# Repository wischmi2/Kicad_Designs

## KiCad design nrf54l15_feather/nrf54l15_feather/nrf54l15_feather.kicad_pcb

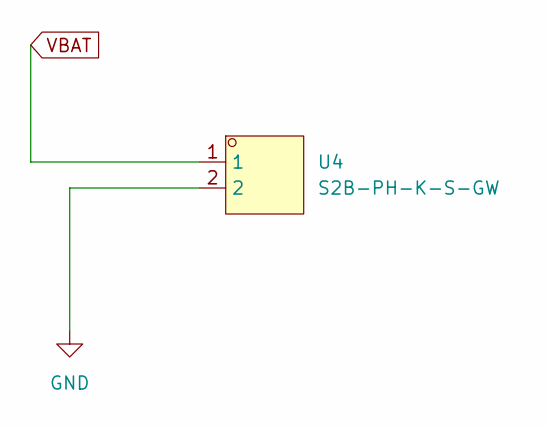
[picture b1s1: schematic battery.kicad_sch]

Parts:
U4: S2B-PH-K-S-GW; CONN-TH_S2B-PH-K-S-GW; MPN S2B-PH-K-S-GW; LCSC Part C157932

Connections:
GND: U4.2; also elsewhere on the board
VBAT: U4.1; also elsewhere on the board

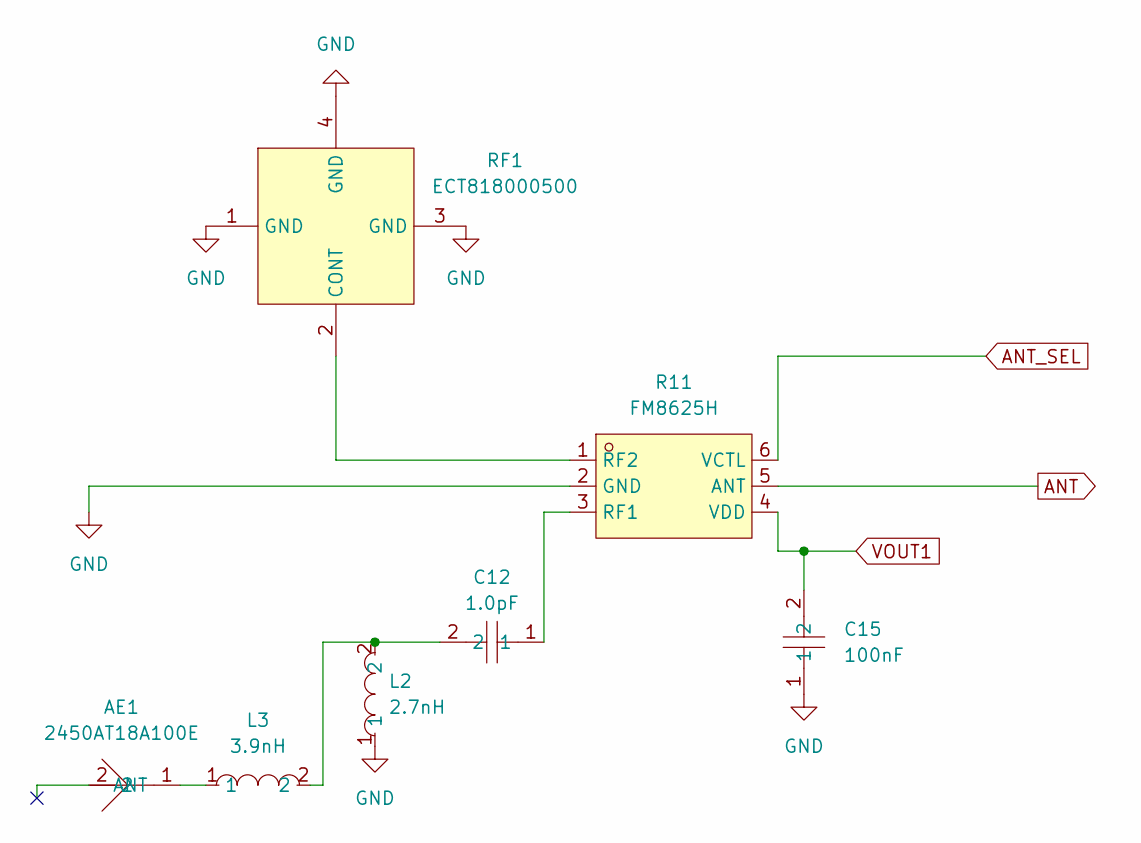
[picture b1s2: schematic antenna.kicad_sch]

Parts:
AE1: 2450AT18A100E; ANT-SMD_L3.2-W1.6; MPN 2450AT18A100E; LCSC Part C89334
C12: 1.0pF; C0201; MPN GJM0335C1E1R0WB01D; LCSC Part C185624
C15: 100nF; C0603; MPN CC0603KRX7R9BB104; LCSC Part C14663
L2: 2.7nH; L0201; MPN LQP03HQ2N7B02D; LCSC Part C7216765
L3: 3.9nH; L0201; MPN LQP03HQ3N9B02D; LCSC Part C337939
R11: FM8625H; DFN-6_L1.1-W0.7-P0.40-BL; MPN FM8625H; LCSC Part C2857391
RF1: ECT818000500; ANT-SMD_ECT818000500; MPN ECT818000500; LCSC Part C437254

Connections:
ANT: R11.5 (ANT); also elsewhere on the board
ANT_SEL: R11.6 (VCTL); also elsewhere on the board
GND: C15.1, L2.1, R11.2 (GND), RF1.1 (GND), RF1.3 (GND), RF1.4 (GND); also elsewhere on the board
unnamed: AE1.1 (ANT_1), L3.1
unnamed: C12.2, L2.2, L3.2
unnamed: C12.1, R11.3 (RF1)
unnamed: R11.1 (RF2), RF1.2 (CONT)
VOUT1: C15.2, R11.4 (VDD); also elsewhere on the board

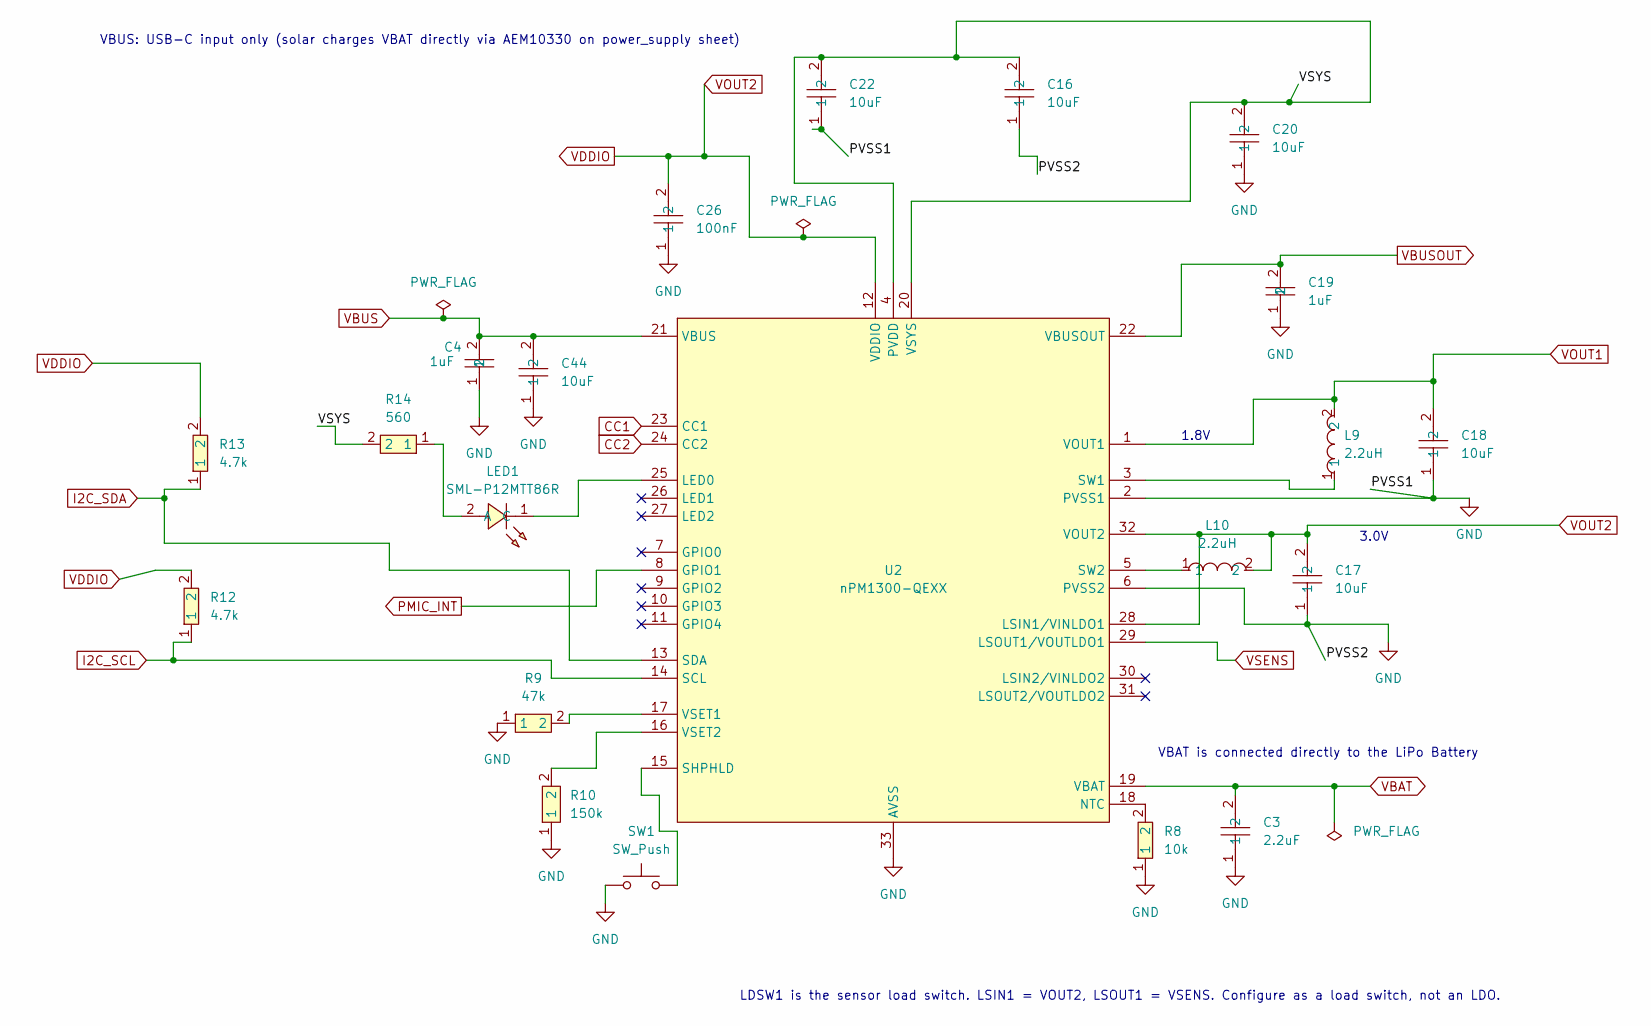
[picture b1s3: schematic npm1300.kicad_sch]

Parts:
C3: 2.2uF; C0603; MPN CL10A225KB8NNNC; LCSC Part C913904
C4, C19: 1uF; C0402; MPN CL05A105KO5NNNC; LCSC Part C29266
C16: 10uF; C0603; MPN CC0603MRX5R8BB106; LCSC Part C596327
C17, C18, C20, C22, C44: 10uF; C0805; MPN CL21A106KAYNNNE; LCSC Part C15850
C26: 100nF; C0603; MPN CC0603KRX7R9BB104; LCSC Part C14663
L9, L10: 2.2uH; L0603; MPN LSCNB1608HKT2R2MD; LCSC Part C6079477
LED1: SML-P12MTT86R; LED-SMD_L1.0-W0.6-RD_SML-P12YTT86RR; MPN SML-P12MTT86R; LCSC Part C510304
R8: 10k; R0402; MPN RT0402BRD0710KL; LCSC Part C190095
R9: 47k; R0603; MPN FRC0603F4702TS; LCSC Part C2907042
R10: 150k; R0603; MPN FRC0603F1503TS; LCSC Part C2906993
R12, R13: 4.7k; R0402; MPN RC0402FR-074K7L; LCSC Part C105871
R14: 560; R0402; MPN FRC0402F5600TS; LCSC Part C2909370
SW1: SW_Push; SW_SPST_B3U-1000P; MPN B3U-1000P
U2: nPM1300-QEXX; QFN-32-1EP_5x5mm_P0.5mm_EP3.6x3.6mm_ThermalVias; MPN nPM1300-QEAA-R7

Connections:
/npm1300/VSYS: C16.2, C20.2, C22.2, R14.2, U2.4 (PVDD), U2.20 (VSYS)
CC1: U2.23 (CC1); also elsewhere on the board
CC2: U2.24 (CC2); also elsewhere on the board
GND: C3.1, C4.1, C16.1, C17.1, C18.1, C19.1, C20.1, C22.1, C26.1, C44.1, R8.1, R9.1, R10.1, SW1.1, U2.2 (PVSS1), U2.6 (PVSS2), U2.33 (AVSS); also elsewhere on the board
I2C_SCL: R12.1, U2.14 (SCL); also elsewhere on the board
I2C_SDA: R13.1, U2.13 (SDA); also elsewhere on the board
unnamed: LED1.2 (A), R14.1
unnamed: LED1.1 (C), U2.25 (LED0)
unnamed: R8.2, U2.18 (NTC)
unnamed: SW1.2, U2.15 (SHPHLD)
unnamed: L9.1, U2.3 (SW1)
unnamed: L10.1, U2.5 (SW2)
unnamed: R9.2, U2.17 (VSET1)
unnamed: R10.2, U2.16 (VSET2)
PMIC_INT: U2.8 (GPIO1); also elsewhere on the board
VBAT: C3.2, U2.19 (VBAT); also elsewhere on the board
VBUS: C4.2, C44.2, U2.21 (VBUS); also elsewhere on the board
VBUSOUT: C19.2, U2.22 (VBUSOUT)
VDDIO: C17.2, C26.2, L10.2, R12.2, R13.2, U2.12 (VDDIO), U2.28 (LSIN1/VINLDO1), U2.32 (VOUT2); also elsewhere on the board
VOUT1: C18.2, L9.2, U2.1 (VOUT1); also elsewhere on the board
VSENS: U2.29 (LSOUT1/VOUTLDO1); also elsewhere on the board

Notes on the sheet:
1.8V
VBAT is connected directly to the LiPo Battery
LDSW1 is the sensor load switch. LSIN1 = VOUT2, LSOUT1 = VSENS. Configure as a load switch, not an LDO.
VBUS: USB-C input only (solar charges VBAT directly via AEM10330 on power_supply sheet)
3.0V

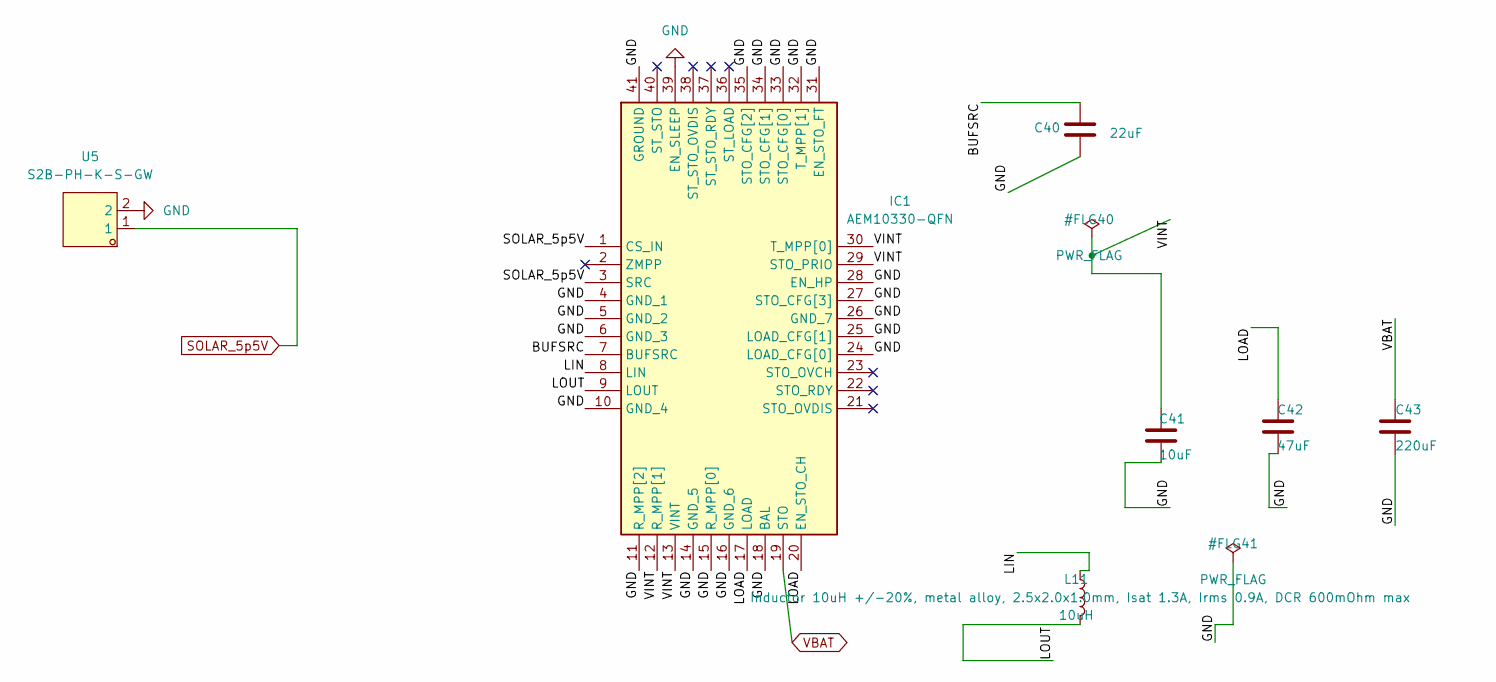
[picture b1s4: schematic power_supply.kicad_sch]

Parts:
C40: 22uF; C_0603_1608Metric; MPN GRM188R61A226ME15D
C41: 10uF; C_0402_1005Metric; MPN GRM155R60J106ME15
C42: 47uF; C_0603_1608Metric; MPN GRM188R60J476ME15D
C43: 220uF; C_1206_3216Metric; MPN MSASJ31LBB5227MTCA01
IC1: AEM10330-QFN; QFN40P500X500X85-41N-D; Mouser Part Number 120-AEM10330-QFN
L11: 10uH; L_Sunlord_SWPA252010S; MPN DFE252010F-100M=P2; LCSC Part C701155
U5: S2B-PH-K-S-GW; CONN-TH_S2B-PH-K-S-GW; MPN S2B-PH-K-S-GW; LCSC Part C157932

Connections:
/Solar/BUFSRC: C40.1, IC1.7 (BUFSRC)
/Solar/LIN: IC1.8 (LIN), L11.1
/Solar/LOAD: C42.1, IC1.17 (LOAD), IC1.20 (EN_STO_CH)
/Solar/LOUT: IC1.9 (LOUT), L11.2
/Solar/VINT: C41.1, IC1.12 (R_MPP[1]), IC1.13 (VINT), IC1.29 (STO_PRIO), IC1.30 (T_MPP[0])
GND: C40.2, C41.2, C42.2, C43.2, IC1.4 (GND_1), IC1.5 (GND_2), IC1.6 (GND_3), IC1.10 (GND_4), IC1.11 (R_MPP[2]), IC1.14 (GND_5), IC1.15 (R_MPP[0]), IC1.16 (GND_6), IC1.18 (BAL), IC1.24 (LOAD_CFG[0]), IC1.25 (LOAD_CFG[1]), IC1.26 (GND_7), IC1.27 (STO_CFG[3]), IC1.28 (EN_HP), IC1.31 (EN_STO_FT), IC1.32 (T_MPP[1]), IC1.33 (STO_CFG[0]), IC1.34 (STO_CFG[1]), IC1.35 (STO_CFG[2]), IC1.39 (EN_SLEEP), IC1.41 (GROUND), U5.2; also elsewhere on the board
SOLAR_5p5V: IC1.1 (CS_IN), IC1.3 (SRC), U5.1
VBAT: C43.1, IC1.19 (STO); also elsewhere on the board

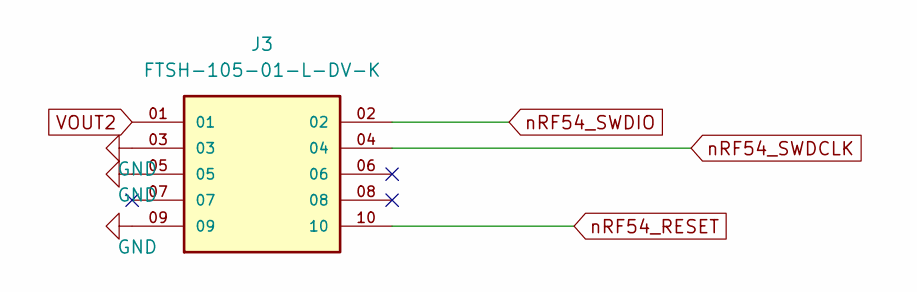
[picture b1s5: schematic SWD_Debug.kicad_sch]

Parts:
J3: FTSH-105-01-L-DV-K; SAMTEC_FTSH-105-01-L-DV-K; MPN FTSH-105-01-L-DV-K-TR

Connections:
GND: J3.03, J3.05, J3.09; also elsewhere on the board
VDDIO: J3.01; also elsewhere on the board
nRF54_RESET: J3.10; also elsewhere on the board
nRF54_SWDCLK: J3.04; also elsewhere on the board
nRF54_SWDIO: J3.02; also elsewhere on the board

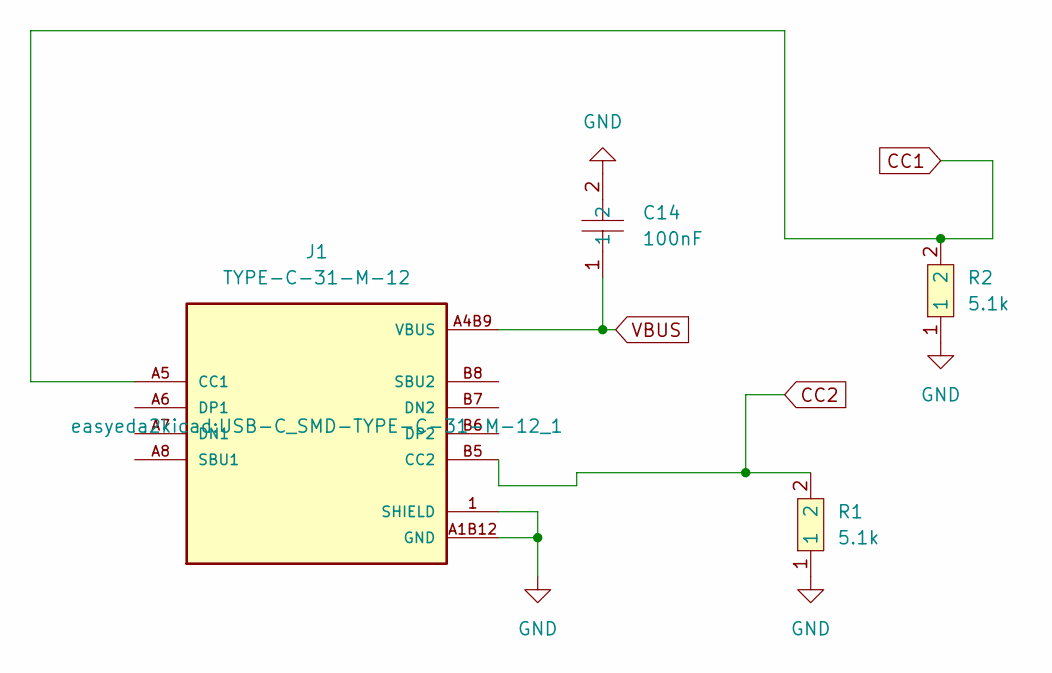
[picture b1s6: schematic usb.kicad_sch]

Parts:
C14: 100nF; C0603; MPN CC0603KRX7R9BB104; LCSC Part C14663
J1: TYPE-C-31-M-12; USB-C_SMD-TYPE-C-31-M-12_1; PARTREV 2020.12.08
R1, R2: 5.1k; R0402; MPN RCA025K1FLF; LCSC Part C22369457

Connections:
CC1: J1.A5 (CC1), R2.2; also elsewhere on the board
CC2: J1.B5 (CC2), R1.2; also elsewhere on the board
GND: C14.2, J1.1 (SHIELD), J1.2 (SHIELD), J1.3 (SHIELD), J1.4 (SHIELD), J1.A1B12 (GND), J1.B1A12 (GND), R1.1, R2.1; also elsewhere on the board
VBUS: C14.1, J1.A4B9 (VBUS), J1.B4A9 (VBUS); also elsewhere on the board

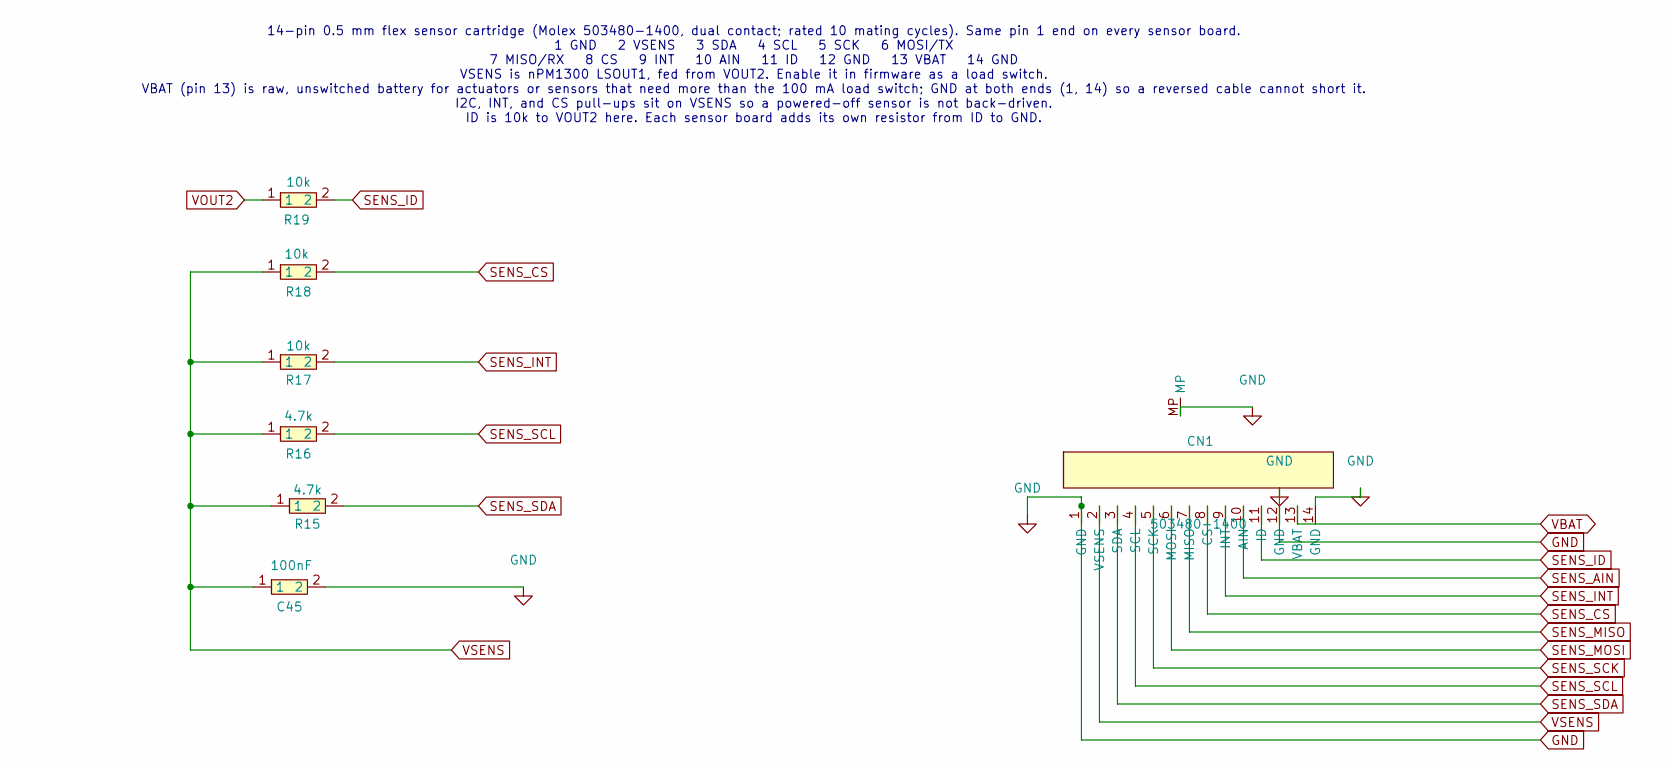
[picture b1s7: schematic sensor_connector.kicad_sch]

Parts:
C45: 100nF; C0402; MPN CL05B104KO5NNNC
CN1: 503480-1400; Molex_503480-1400_1x14-1MP_P0.50mm_Horizontal; MPN 503480-1400
R15, R16: 4.7k; R0402; MPN RC0402FR-074K7L
R17, R18, R19: 10k; R0402; MPN RT0402BRD0710KL; LCSC Part C190095

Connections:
GND: C45.2, CN1.1 (GND), CN1.12 (GND), CN1.14 (GND), CN1.MP; also elsewhere on the board
SENS_AIN: CN1.10 (AIN); also elsewhere on the board
SENS_CS: CN1.8 (CS), R18.2; also elsewhere on the board
SENS_ID: CN1.11 (ID), R19.2; also elsewhere on the board
SENS_INT: CN1.9 (INT), R17.2; also elsewhere on the board
SENS_MISO: CN1.7 (MISO); also elsewhere on the board
SENS_MOSI: CN1.6 (MOSI); also elsewhere on the board
SENS_SCK: CN1.5 (SCK); also elsewhere on the board
SENS_SCL: CN1.4 (SCL), R16.2; also elsewhere on the board
SENS_SDA: CN1.3 (SDA), R15.2; also elsewhere on the board
VBAT: CN1.13 (VBAT); also elsewhere on the board
VDDIO: R19.1; also elsewhere on the board
VSENS: C45.1, CN1.2 (VSENS), R15.1, R16.1, R17.1, R18.1; also elsewhere on the board

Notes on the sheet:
14-pin 0.5 mm flex sensor cartridge (Molex 503480-1400, dual contact; rated 10 mating cycles). Same pin 1 end on every sensor board. 1 GND 2 VSENS 3 SDA 4 SCL 5 SCK 6 MOSI/TX 7 MISO/RX 8 CS 9 INT 10 AIN 11 ID 12 GND 13 VBAT 14 GND VSENS is nPM1300 LSOUT1, fed from VOUT2. Enable it in firmware as a 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

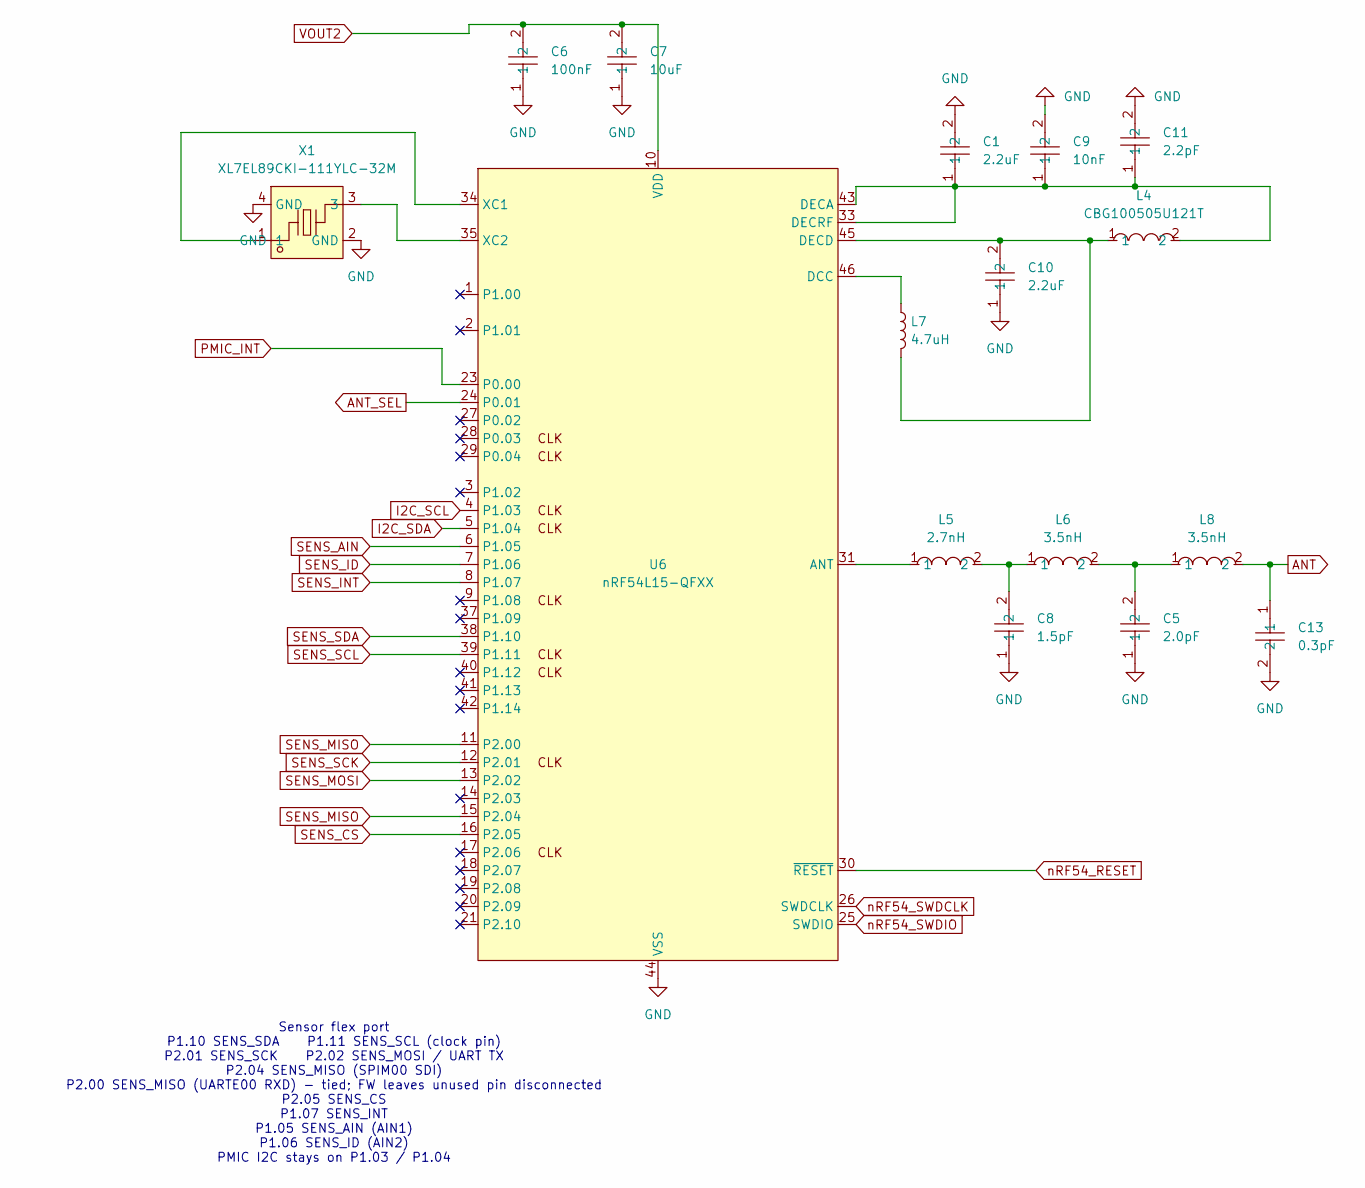
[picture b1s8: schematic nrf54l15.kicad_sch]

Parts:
C1, C10: 2.2uF; C0201; MPN GRM033R61A225KE47D; LCSC Part C335106
C5: 2.0pF; C0201; MPN GJM0335C1E2R0WB01D; LCSC Part C668326
C6: 100nF; C0603; MPN CC0603KRX7R9BB104; LCSC Part C14663
C7: 10uF; C0805; MPN CL21A106KAYNNNE; LCSC Part C15850
C8: 1.5pF; C0201; MPN GJM0335C1E1R5WB01D; LCSC Part C435397
C9: 10nF; C0402; MPN GCM155R71H103KA55D; LCSC Part C91601
C11: 2.2pF; C0201; MPN GJM0335C1E2R2WB01D; LCSC Part C710732
C13: 0.3pF; C0201; MPN GJM0335C1ER30WB01D; LCSC Part C161289
L4: CBG100505U121T; L0402; MPN CBG100505U121T; LCSC Part C92616
L5: 2.7nH; L0201; MPN LQP03HQ2N7B02D; LCSC Part C7216765
L6, L8: 3.5nH; L0201; MPN LQP03HQ3N5B02D; LCSC Part C3911055
L7: 4.7uH; L0603; MPN LQM18PH4R7MFRL; LCSC Number C1858257
U6: nRF54L15-QFXX; QFN-48-1EP_6x6mm_P0.4mm_EP4.6x4.6mm_ThermalVias; MPN nRF54L15-QFAA-R
X1: XL7EL89CKI-111YLC-32M; CRYSTAL-SMD_4P-L2.0-W1.6-BL; MPN XL7EL89CKI-111YLC-32M; LCSC Part C2965582

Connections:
ANT: C13.1, L8.2; also elsewhere on the board
ANT_SEL: U6.24 (P0.01); also elsewhere on the board
GND: C1.2, C5.1, C6.1, C7.1, C8.1, C9.2, C10.1, C11.2, C13.2, U6.32 (VSS_PA), U6.44 (VSS), U6.49 (VSS), X1.2 (GND), X1.4 (GND); also elsewhere on the board
I2C_SCL: U6.4 (P1.03); also elsewhere on the board
I2C_SDA: U6.5 (P1.04); also elsewhere on the board
unnamed: C5.2, L6.2, L8.1
unnamed: C8.2, L5.2, L6.1
unnamed: L5.1, U6.31 (ANT)
unnamed: L7.1, U6.46 (DCC)
unnamed: C1.1, C9.1, C11.1, L4.2, U6.33 (DECRF), U6.43 (DECA)
unnamed: C10.2, L4.1, L7.2, U6.45 (DECD)
unnamed: U6.34 (XC1), X1.1
unnamed: U6.35 (XC2), X1.3
PMIC_INT: U6.23 (P0.00); also elsewhere on the board
SENS_AIN: U6.6 (P1.05); also elsewhere on the board
SENS_CS: U6.16 (P2.05); also elsewhere on the board
SENS_ID: U6.7 (P1.06); also elsewhere on the board
SENS_INT: U6.8 (P1.07); also elsewhere on the board
SENS_MISO: U6.11 (P2.00), U6.15 (P2.04); also elsewhere on the board
SENS_MOSI: U6.13 (P2.02); also elsewhere on the board
SENS_SCK: U6.12 (P2.01); also elsewhere on the board
SENS_SCL: U6.39 (P1.11); also elsewhere on the board
SENS_SDA: U6.38 (P1.10); also elsewhere on the board
VDDIO: C6.2, C7.2, U6.10 (VDD), U6.22 (VDD), U6.36 (VDD), U6.47 (VDD), U6.48 (VDD); also elsewhere on the board
nRF54_RESET: U6.30 (~RESET); also elsewhere on the board
nRF54_SWDCLK: U6.26 (SWDCLK); also elsewhere on the board
nRF54_SWDIO: U6.25 (SWDIO); also elsewhere on the board

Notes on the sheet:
Sensor flex port P1.10 SENS_SDA P1.11 SENS_SCL (clock pin) P2.01 SENS_SCK P2.02 SENS_MOSI / UART TX P2.04 SENS_MISO (SPIM00 SDI) P2.00 SENS_MISO (UARTE00 RXD) - tied; FW leaves unused pin disconnected P2.05 SENS_CS P1.07 SENS_INT P1.05 SENS_AIN (AIN1) P1.06 SENS_ID (AIN2) PMIC I2C stays on P1.03 / 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

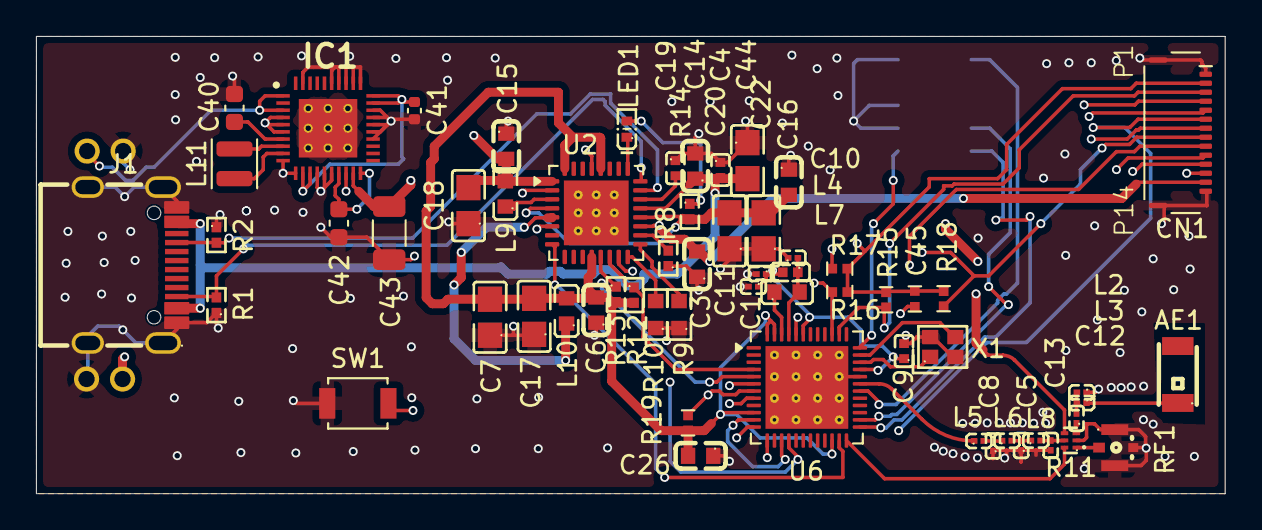
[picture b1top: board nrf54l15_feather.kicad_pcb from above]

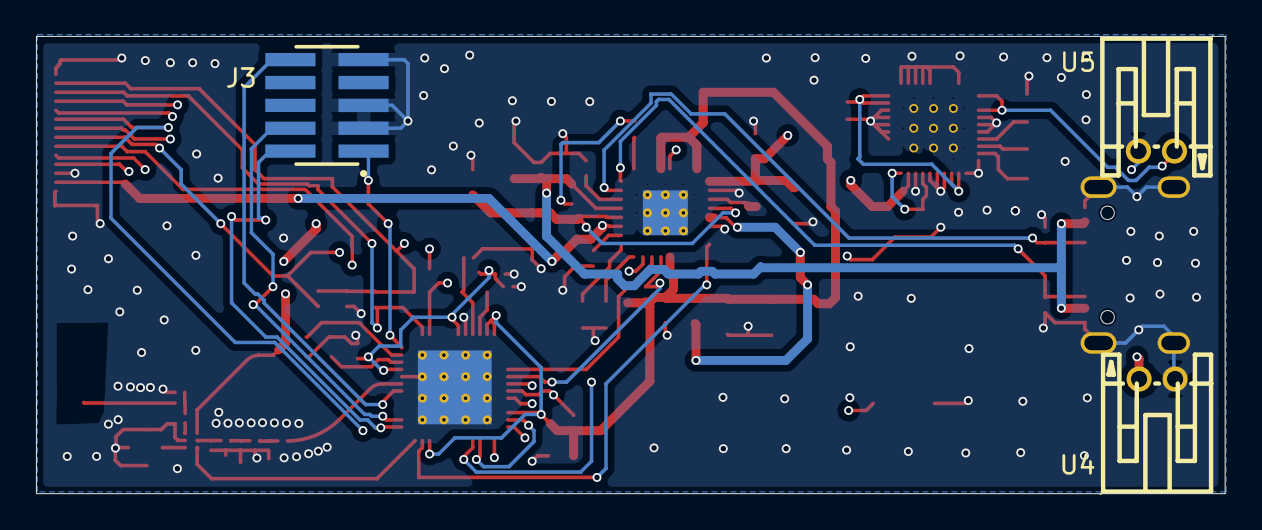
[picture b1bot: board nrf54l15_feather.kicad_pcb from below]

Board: 4 copper layers, 66.0 x 25.4 mm, 64 parts (3 on the bottom side), 53 nets.

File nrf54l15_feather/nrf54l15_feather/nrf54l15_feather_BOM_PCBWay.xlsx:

|  |  | nrf54l15_feather — PCB Assembly BOM
Item # | *Designator | *Qty | Manufacturer | *Mfg Part # | Description / Value | *Package/Footprint | Type | Your Instructions / Notes
1 | C45 | 1 | Samsung Electro-Mechanics | CL05B104KO5NNNC | CAP CER 100nF 16V X7R ±10% 0402 | 0402 | SMD | LCSC: C1525
2 | C6,C14,C15,C26 | 4 | YAGEO | CC0603KRX7R9BB104 | CAP CER 100nF 50V X7R ±10% 0603 | 0603 | SMD | LCSC: C14663
3 | C9 | 1 | Murata | GCM155R71H103KA55D | CAP CER 10nF 50V X7R ±10% 0402 | 0402 | SMD | LCSC: C91601
4 | C4,C19 | 2 | Samsung Electro-Mechanics | CL05A105KO5NNNC | CAP CER 1uF 16V X5R ±10% 0402 | 0402 | SMD | LCSC: C29266
5 | C1,C10 | 2 | Murata | GRM033R61A225KE47D | CAP CER 2.2uF 10V X5R ±10% 0201 | 0201 | SMD | LCSC: C335106
6 | C3 | 1 | Samsung Electro-Mechanics | CL10A225KB8NNNC | CAP CER 2.2uF 50V X5R ±10% 0603 | 0603 | SMD | LCSC: C913904
7 | C41 | 1 | Murata | GRM155R60J106ME15 | CAP CER 10uF 6.3V X5R ±20% 0402 | 0402 | SMD | No LCSC stock for ME15; GRM155R60J106ME44D (LCSC: C76991) acceptable alternate
8 | C16 | 1 | YAGEO | CC0603MRX5R8BB106 | CAP CER 10uF 25V X5R ±20% 0603 | 0603 | SMD | LCSC: C596327
9 | C7,C17,C18,C20,C22,C44 | 6 | Samsung Electro-Mechanics | CL21A106KAYNNNE | CAP CER 10uF 25V X5R ±10% 0805 | 0805 | SMD | LCSC: C15850
10 | C40 | 1 | Murata | GRM188R61A226ME15D | CAP CER 22uF 10V X5R ±20% 0603 | 0603 | SMD | LCSC: C84419
11 | C42 | 1 | Murata | GRM188R60J476ME15D | CAP CER 47uF 6.3V X5R ±20% 0603 | 0603 | SMD | LCSC: C140782
12 | C43 | 1 | Taiyo Yuden | MSASJ31LBB5227MTCA01 | CAP CER 220uF 1206 | 1206 | SMD | No LCSC part #; please quote sourcing
13 | C13 | 1 | Murata | GJM0335C1ER30WB01D | CAP CER 0.3pF 25V C0G ±0.05pF 0201 (RF) | 0201 | SMD | LCSC: C161289; RF match — do not substitute
14 | C12 | 1 | Murata | GJM0335C1E1R0WB01D | CAP CER 1.0pF 25V C0G ±0.05pF 0201 (RF) | 0201 | SMD | LCSC: C185624; RF match — do not substitute
15 | C8 | 1 | Murata | GJM0335C1E1R5WB01D | CAP CER 1.5pF 25V C0G ±0.05pF 0201 (RF) | 0201 | SMD | LCSC: C435397; RF match — do not substitute
16 | C5 | 1 | Murata | GJM0335C1E2R0WB01D | CAP CER 2.0pF 25V C0G ±0.05pF 0201 (RF) | 0201 | SMD | LCSC: C668326; RF match — do not substitute
17 | C11 | 1 | Murata | GJM0335C1E2R2WB01D | CAP CER 2.2pF 25V C0G ±0.05pF 0201 (RF) | 0201 | SMD | LCSC: C710732; RF match — do not substitute
18 | R14 | 1 | FOJAN | FRC0402F5600TS | RES 560 OHM 1% 0402 | 0402 | SMD | LCSC: C2909370
19 | R12,R13,R15,R16 | 4 | YAGEO | RC0402FR-074K7L | RES 4.7K OHM 1% 1/16W 0402 | 0402 | SMD | LCSC: C105871
20 | R1,R2 | 2 | HKR | RCA025K1FLF | RES 5.1K OHM 1% 0402 | 0402 | SMD | LCSC: C22369457
21 | R8,R17,R18,R19 | 4 | YAGEO | RT0402BRD0710KL | RES 10K OHM 0.1% 0402 | 0402 | SMD | LCSC: C190095
22 | R9 | 1 | FOJAN | FRC0603F4702TS | RES 47K OHM 1% 0603 | 0603 | SMD | LCSC: C2907042
23 | R10 | 1 | FOJAN | FRC0603F1503TS | RES 150K OHM 1% 0603 | 0603 | SMD | LCSC: C2906993
24 | L2,L5 | 2 | Murata | LQP03HQ2N7B02D | INDUCTOR RF 2.7nH ±0.1nH 0201 | 0201 | SMD | LCSC: C7216765; RF match — do not substitute
25 | L6,L8 | 2 | Murata | LQP03HQ3N5B02D | INDUCTOR RF 3.5nH ±0.1nH 0201 | 0201 | SMD | LCSC: C3911055; RF match — do not substitute
26 | L3 | 1 | Murata | LQP03HQ3N9B02D | INDUCTOR RF 3.9nH ±0.1nH 0201 | 0201 | SMD | LCSC: C337939; RF match — do not substitute
27 | L4 | 1 | FH (Fenghua) | CBG100505U121T | FERRITE BEAD 120 OHM @100MHz 0402 | 0402 | SMD | LCSC: C92616
28 | L9,L10 | 2 | Taiyo Yuden | LSCNB1608HKT2R2MD | INDUCTOR PWR 2.2uH ±20% 0603 | 0603 | SMD | LCSC: C6079477
29 | L7 | 1 | Murata | LQM18PH4R7MFRL | INDUCTOR PWR 4.7uH ±20% 0603 | 0603 | SMD | LCSC: C1858257
30 | L11 | 1 | Murata | DFE252010F-100M=P2 | INDUCTOR PWR 10uH ±20% 2.5x2.0mm | SMD 2.5x2.0mm | SMD | LCSC: C701155
31 | LED1 | 1 | ROHM | SML-P12MTT86R | LED RED 1006 (0402) | 1006 (0402) | SMD | LCSC: C510304; polarity per silkscreen
32 | U6 | 1 | Nordic Semiconductor | nRF54L15-QFAA-R | IC SoC BLE 2.4GHz ARM Cortex-M33 QFN-48 6x6mm | QFN-48 6x6mm P0.4mm | SMD | LCSC: C42458750; pin 1 per silkscreen
33 | U2 | 1 | Nordic Semiconductor | nPM1300-QEAA-R7 | IC PMIC CHARGER + 2x BUCK + 2x LDO/LOAD SW QFN-32 5x5mm | QFN-32 5x5mm P0.5mm | SMD | QFN-32 package required (do NOT substitute CSP variant); please quote sourcing.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
34 | IC1 | 1 | e-peas | AEM10330-QFN | IC ENERGY HARVESTING PMIC (solar) QFN-40 5x5mm | QFN-40 5x5mm P0.4mm | SMD | No LCSC part #; Mouser: 120-AEM10330-QFN; please quote sourcing. Pin 1 per silk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
35 | R11 | 1 | FM (Fuman) | FM8625H | IC RF SWITCH SPDT DFN-6 1.1x0.7mm | DFN-6 1.1x0.7mm P0.4mm | SMD | LCSC: C2857391; this is an IC (not a resistor) despite R designator. Pin 1 per 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
36 | X1 | 1 | YXC | XL7EL89CKI-111YLC-32M | CRYSTAL 32MHz SMD 2.0x1.6mm 4-pad | SMD 2.0x1.6mm | SMD | LCSC: C2965582
37 | AE1 | 1 | Johanson Technology | 2450AT18A100E | ANTENNA CHIP 2.45GHz 3.2x1.6mm | SMD 3.2x1.6mm | SMD | LCSC: C89334; orientation per silkscreen
38 | RF1 | 1 | ECT | ECT818000500 | CONN RF COAX RCPT SMD | SMD | SMD | LCSC: C437254
39 | J1 | 1 | Korean Hroparts Elec (HRO) | TYPE-C-31-M-12 | CONN USB TYPE-C RCPT 16P SMD R/A | SMD | SMD | LCSC: C165948
40 | CN1 | 1 | Molex | 503480-1400 | CONN FFC/FPC 14POS 0.5mm R/A SMD | 1x14 P0.50mm SMD | SMD | No LCSC part #; please quote sourcing. Pin 1 per silkscreen
41 | J3 | 1 | Samtec | FTSH-105-01-L-DV-K-TR | CONN HDR 2x5 1.27mm SMD VERT (SWD) | 2x5 P1.27mm SMD | SMD | LCSC: C448647; BOTTOM SIDE. Pin 1 per silkscreen
42 | SW1 | 1 | Omron | B3U-1000P | SWITCH TACTILE SPST-NO SMD 3.0x2.5mm | SMD 3.0x2.5mm | SMD | No LCSC part # assigned; please quote sourcing
43 | U4,U5 | 2 | JST | S2B-PH-K-S-GW | CONN HDR PH 2POS 2.0mm R/A THT | 1x2 P2.00mm R/A THT | thru-hole | LCSC: C157932; BOTTOM SIDE
Need a quick and accurante quote? Need an efficient production? Please read SMT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
Click for Instructions on How to Create a BOM

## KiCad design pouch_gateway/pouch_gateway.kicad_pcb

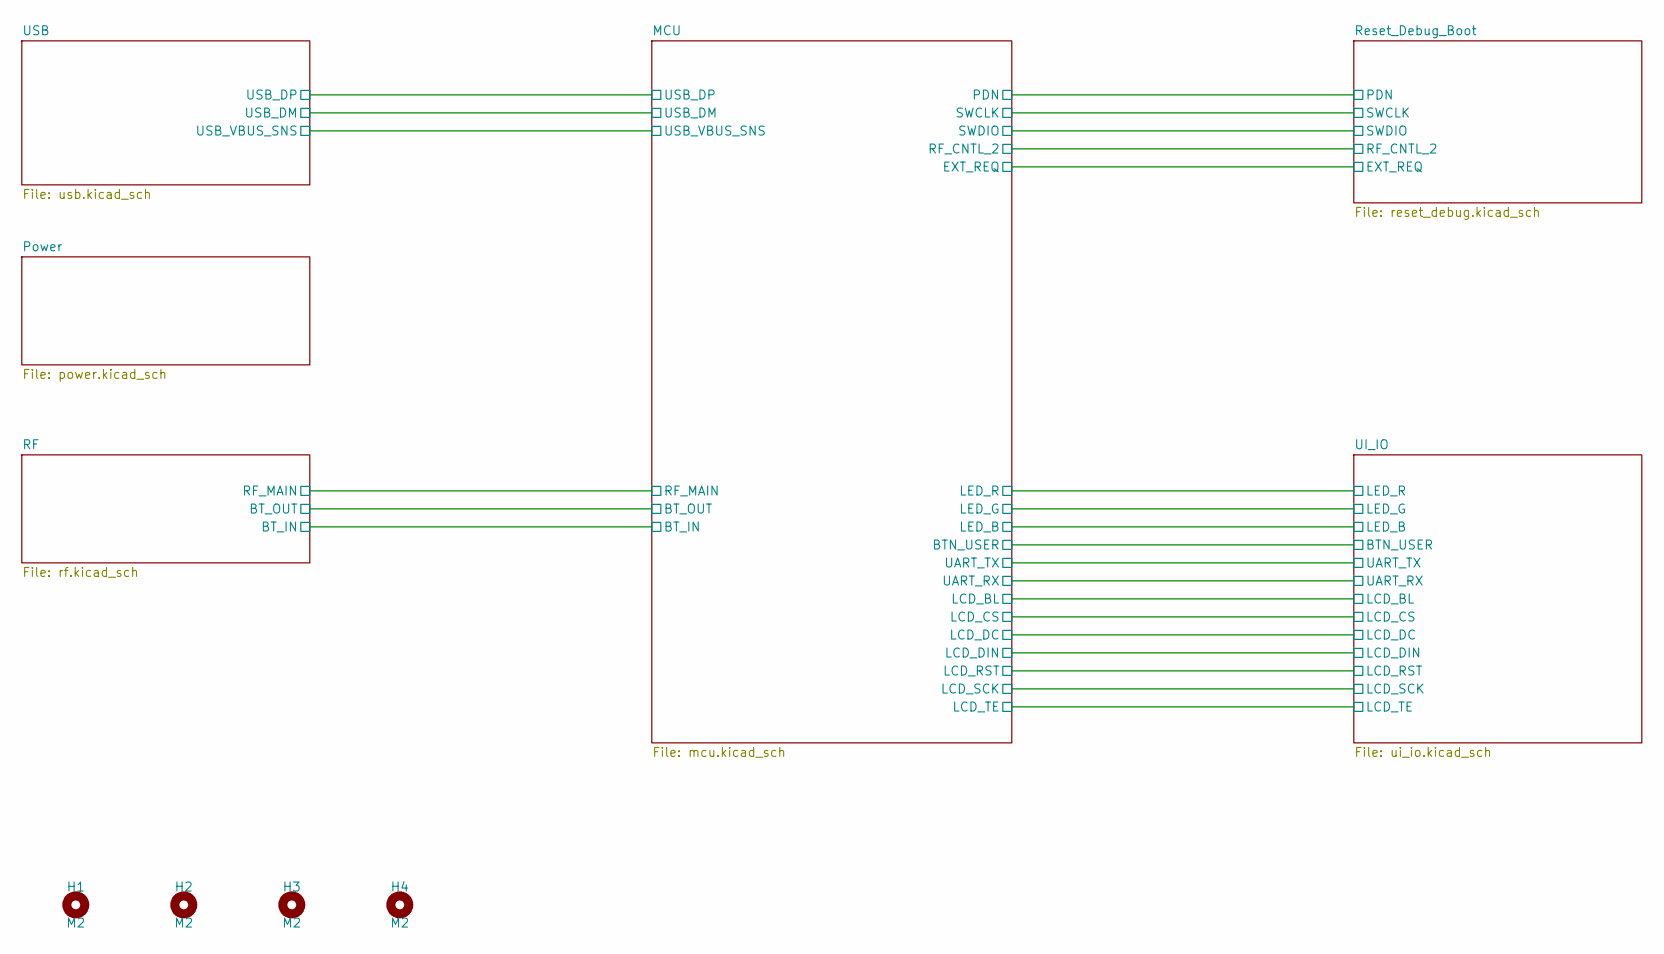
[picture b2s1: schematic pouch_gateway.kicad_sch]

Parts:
H1, H2, H3, H4: M2; MountingHole_2.2mm_M2

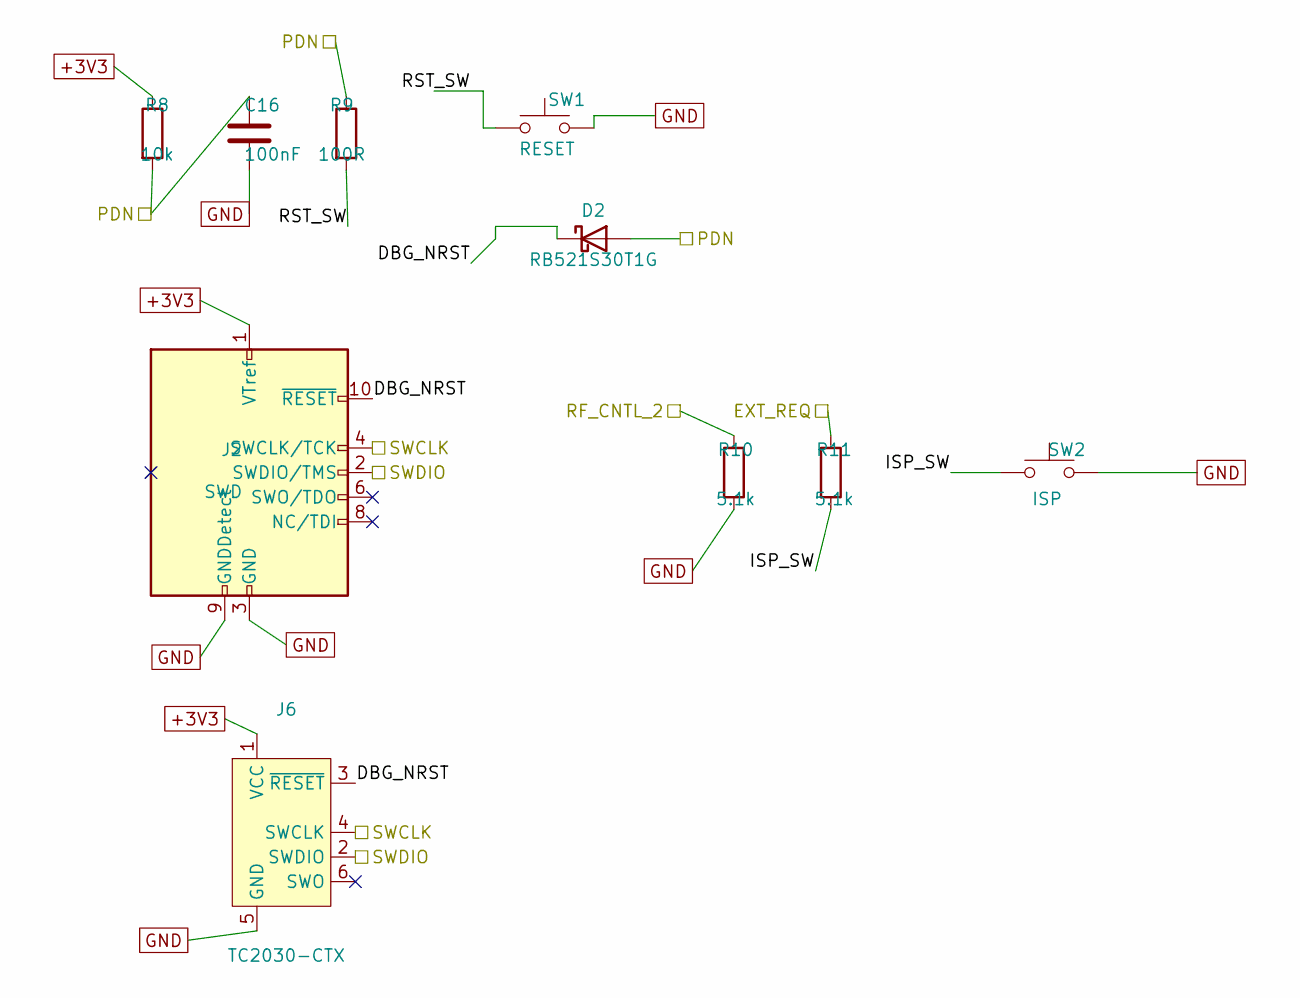
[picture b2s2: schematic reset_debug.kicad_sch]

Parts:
C16: 100nF; C_0402_1005Metric; LCSC C1525
D2: RB521S30T1G; D_SOD-523; LCSC C145179
J2: SWD; PinHeader_2x05_P1.27mm_Vertical_SMD; MPN FTSH-105-01-L-DV-K-TR; LCSC C448647
J6: TC2030-CTX; Tag-Connect_TC2030-IDC-FP_2x03_P1.27mm_Vertical
R8: 10k; R_0402_1005Metric; LCSC C25744
R9: 100R; R_0402_1005Metric; LCSC C25076
R10, R11: 5.1k; R_0402_1005Metric; LCSC C25905
SW1: RESET; SW_Push_1P1T_NO_CK_KMR2; LCSC C72443
SW2: ISP; SW_Push_1P1T_NO_CK_KMR2; LCSC C72443

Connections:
+3V3: J2.1 (VTref), J6.1 (VCC), R8.1; also elsewhere on the board
/MCU/EXT_REQ: R11.1; also elsewhere on the board
/MCU/PDN: C16.1, D2.2 (A), R8.2, R9.1; also elsewhere on the board
/MCU/RF_CNTL_2: R10.1; also elsewhere on the board
/MCU/SWCLK: J2.4 (SWCLK/TCK), J6.4 (SWCLK); also elsewhere on the board
/MCU/SWDIO: J2.2 (SWDIO/TMS), J6.2 (SWDIO); also elsewhere on the board
/Reset_Debug_Boot/DBG_NRST: D2.1 (K), J2.10 (~RESET), J6.3 (~RESET)
/Reset_Debug_Boot/ISP_SW: R11.2, SW2.1; also elsewhere on the board
/Reset_Debug_Boot/RST_SW: R9.2, SW1.1; also elsewhere on the board
GND: C16.2, J2.3 (GND), J2.5 (GND), J2.9 (GNDDetect), J6.5 (GND), R10.2, SW1.2, SW2.2; also elsewhere on the board
